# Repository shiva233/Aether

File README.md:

# Aether 🎧
 
A USB-C powered Bluetooth-to-USB audio bridge that lets me connect my phone / Steam Deck with Bluetooth and send that audio straight into my PC as a USB audio input!

|  |  |
| :---: | :---: |
|  |  |

What is Aether? :0

Aether is basically a small USB-C dongle/box thing that pairs to my iPhone, Steam Deck, or other Bluetooth audio source, receives the audio wirelessly, and then sends it to my PC over USB so the computer sees it like a normal USB microphone / audio input device.

I wanted this because very often I want to mix audio from my Steam Deck or phone into my PC headphones while on call with friends or watching a movie, without needing random software, aux cables, capture cards, or weird Windows audio routing. So the idea is that Aether just sits between the device and my PC:

Phone / Steam Deck → Bluetooth → Aether → USB-C → PC → My ears :D

The project is also kind of a challenge project for me because it combines Bluetooth Classic audio, I2S digital audio, USB Audio Class, USB-C power/data, and a custom PCB power tree all in one board :D

## Block Diagram
Coming soon, I promise!! I just need to make a cleaner one!!

## Schematics:

## Layout:

|  |  |
| :---: | :---: |
| <br><b>Top Layer</b> | <br><b>Bottom Layer</b> |
| <br><b>Inner Layer</b> | <br><b>Inner Layer</b> |

Extra Info:

- The Bluetooth Module: Microchip BM83 Bluetooth Stereo Audio Module
- The MCU: STM32C552CET6
- Bluetooth: Bluetooth Classic A2DP Sink
- Audio Path: BM83 decodes Bluetooth audio and outputs digital PCM over I2S
- USB: USB 2.0 Full-Speed device over USB-C
- PC Interface: USB Audio Class input device so Windows can recognize it without custom drivers
- Power: Powered fully from the PC through USB-C VBUS
- BM83 Power Rail: 3.6V Buck Regulator 
- STM32 Power Rail: 3.3V LDO
- Stackup: 4-Layer Custom PCB (Signal - GND - GND - Signal)

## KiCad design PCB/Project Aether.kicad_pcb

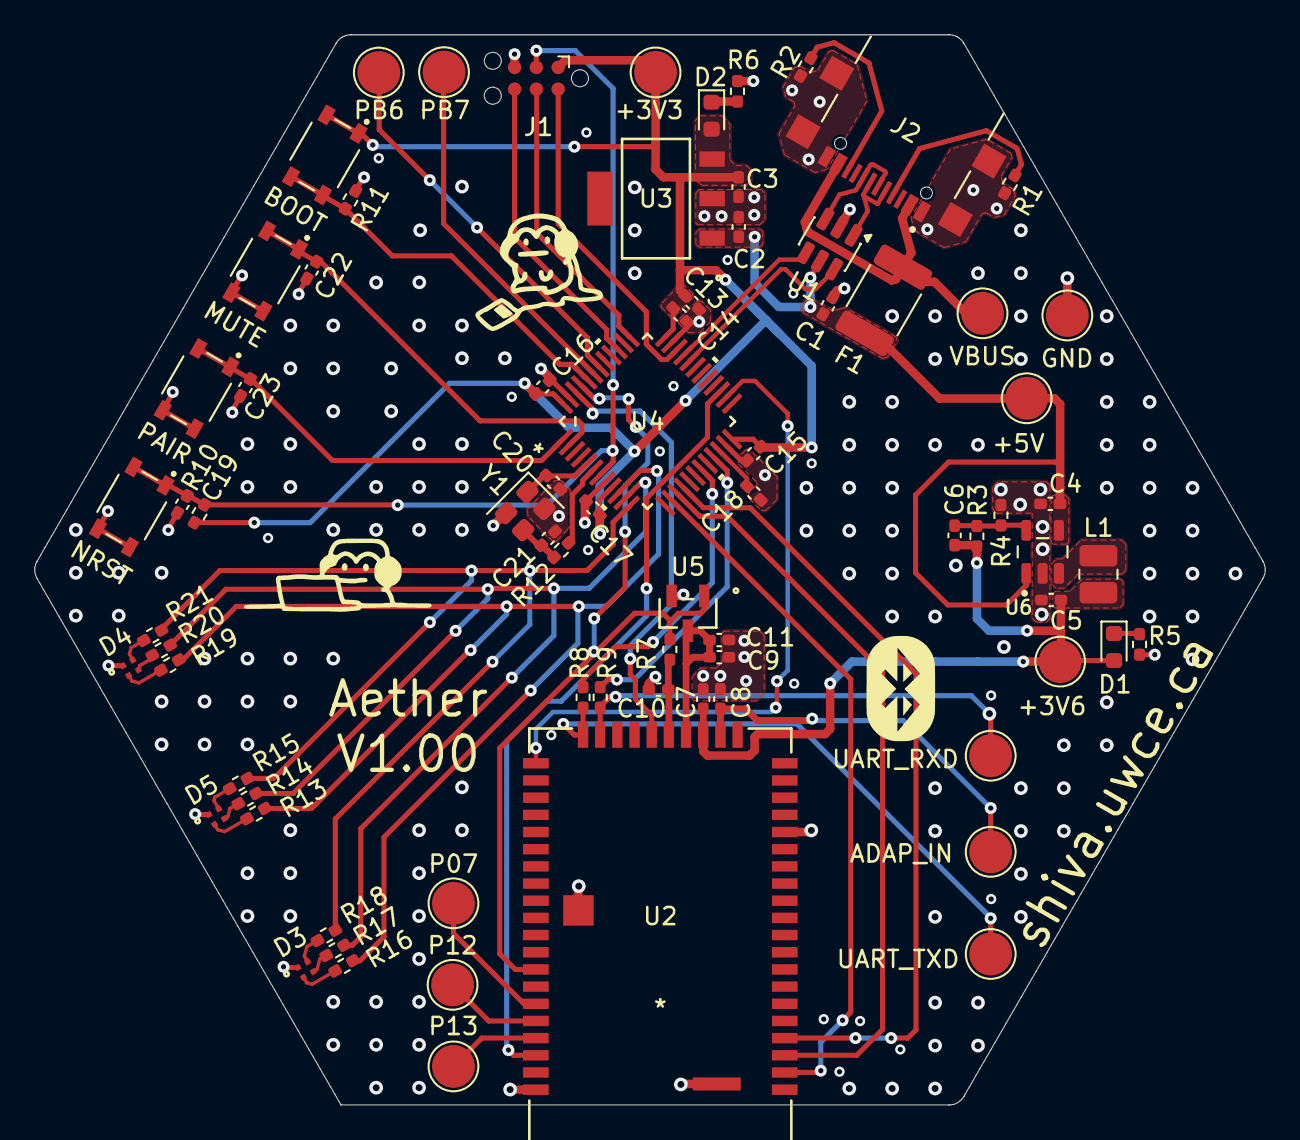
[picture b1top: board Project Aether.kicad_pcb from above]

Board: 4 copper layers, 71.7 x 62.4 mm, 76 parts (0 on the bottom side), 57 nets.

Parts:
+3V3: +3V3; TestPoint_Pad_D2.5mm
+3V6: +3V6; TestPoint_Pad_D2.5mm
+5V: +5V; TestPoint_Pad_D2.5mm
ADAP_IN: TestPoint; TestPoint_Pad_D2.5mm
BOOT: BOOT; SW_SKRPACE010
C1: 100nF; C_0402_1005Metric_Pad0.74x0.62mm_HandSolder
C2, C3, C4, C5: 10uF; C_0402_1005Metric_Pad0.74x0.62mm_HandSolder
C6: DNP; C_0402_1005Metric_Pad0.74x0.62mm_HandSolder
C7, C8: 1uF; C_0402_1005Metric_Pad0.74x0.62mm_HandSolder
C9, C10, C11, C14, C15, C16, C17, C19, C22, C23: 0.1uF; C_0402_1005Metric_Pad0.74x0.62mm_HandSolder
C13: 4.7uF; C_0402_1005Metric_Pad0.74x0.62mm_HandSolder
C18: 2.2uF; C_0402_1005Metric_Pad0.74x0.62mm_HandSolder
C20, C21: 10pF; C_0402_1005Metric_Pad0.74x0.62mm_HandSolder
D1, D2: GREEN; LED_0603_1608Metric
D3, D4, D5: LED_ARGB; SMD4_UHD111A-FKA_CRW
F1: 0.5A HOLD PTC; Fuse_1812_4532Metric_Pad1.30x3.40mm_HandSolder
GND: GND; TestPoint_Pad_D2.5mm
J1: TagConnect; Tag-Connect_TC2030-IDC-NL_2x03_P1.27mm_Vertical
J2: GSB1C41110SSHR; AMPHENOL_GSB1C41110SSHR
L1: 10uH; L_1008_2520Metric
MUTE: MUTE; SW_SKRPACE010
NRST: RESET; SW_SKRPACE010
P07, P12, P13: TestPoint; TestPoint_Pad_D2.5mm
PAIR: PAIR; SW_SKRPACE010
PB6, PB7: TestPoint; TestPoint_Pad_D2.5mm
R1, R2: 5K1; R_0402_1005Metric_Pad0.72x0.64mm_HandSolder
R3: 100k; R_0402_1005Metric_Pad0.72x0.64mm_HandSolder
R4: 20k; R_0402_1005Metric_Pad0.72x0.64mm_HandSolder
R5, R6: 820R; R_0402_1005Metric_Pad0.72x0.64mm_HandSolder
R7: 4.7k; R_0402_1005Metric_Pad0.72x0.64mm_HandSolder
R8, R9, R12: 0R; R_0402_1005Metric_Pad0.72x0.64mm_HandSolder
R10, R11: 10k; R_0402_1005Metric_Pad0.72x0.64mm_HandSolder
R13, R14, R15, R16, R17, R18, R19, R20, R21: TODO; R_0402_1005Metric_Pad0.72x0.64mm_HandSolder
U1: USBLC6-2SC6; SOT-23-6
U2: BM83SM1-00TB; BM83_MCH
U3: MCP1825S-3302E/DB; SOT-223_3MC_MCH
U4: STM32C552CET6; LQFP-48_STM
U5: MCP111T-300E/TT; SOT-23_MC_MCH
U6: TLV62569DBVR; SOT95P280X145-5N
UART_RXD: TestPoint; TestPoint_Pad_D2.5mm
UART_TXD: TestPoint; TestPoint_Pad_D2.5mm
VBUS: VBUS; TestPoint_Pad_D2.5mm
Y1: 16Mhz; Crystal_SMD_2520-4Pin_2.5x2.0mm

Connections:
+3V3: +3V3.1 (1_1), BOOT.1, BOOT.3, C3.2, C13.1, C14.1, C15.1, C16.1, C17.1, D2.2 (A), J1.1 (VCC), R10.1, U3.3 (VOUT), U4.9 (VREF+), U4.24 (VDD), U4.36 (VDD), U4.48 (VDD)
+3V6: +3V6.1 (1_1), C5.2, C6.2, C7.1, D1.2 (A), L1.2, R3.1, U2.23 (BAT_IN)
+5V: +5V.1 (1_1), C1.2, C2.2, C4.2, F1.2, U1.5 (VBUS), U3.1 (VIN), U6.1 (EN), U6.4 (VIN)
/MCU/BM83_ADAP_IN: ADAP_IN.1 (1_1), C8.1, U2.22 (ADAP_IN)
/MCU/BM83_MFB: U2.26 (PWR(MFB)), U4.46 (PB9)
/MCU/BM83_P0_7: P07.1 (1_1), U2.45 (P0_7)
/MCU/BM83_P1_2: P12.1 (1_1), U2.46 (P1_2/TDI_CPU/SCL)
/MCU/BM83_P1_3: P13.1 (1_1), U2.47 (P1_3/TCK_CPU/SDA)
/MCU/BM83_RESET_N: R7.2, U2.43 (RST_N), U4.45 (PB8), U5.1 (VOUT)
/MCU/BM83_UART_RXD: R9.2, U2.29 (P8_6/UART_RXD), UART_RXD.1 (1_1)
/MCU/BM83_UART_TXD: R8.2, U2.30 (P8_5/UART_TXD), UART_TXD.1 (1_1)
/MCU/STM_BOOT0: BOOT.2, BOOT.4, R11.1, U4.44 (PH2-BOOT0)
/MCU/STM_HSE_IN: C20.1, U4.5 (PH0-OSC_IN), Y1.1
/MCU/STM_HSE_OUT: R12.1, U4.6 (PH1-OSC_OUT)
/MCU/STM_I2S_CK: U2.3 (SCLK1), U4.15 (PA5)
/MCU/STM_I2S_SDI: U2.4 (DT1), U4.16 (PA6)
/MCU/STM_I2S_WS: U2.2 (RFS1), U4.14 (PA4)
/MCU/STM_MUTE_BTN: C22.1, MUTE.1, MUTE.3, U4.2 (PC13)
/MCU/STM_NRST: C19.1, J1.3 (~RESET), NRST.1, NRST.3, R10.2, U4.7 (NRST)
/MCU/STM_PAIR_BTN: C23.1, PAIR.1, PAIR.3, U4.1 (PE2)
/MCU/STM_PB6: PB6.1 (1_1), U4.42 (PB6)
/MCU/STM_PB7: PB7.1 (1_1), U4.43 (PB7)
/MCU/STM_RGB_B: R15.1, R18.1, R21.1, U4.12 (PA2)
/MCU/STM_RGB_G: R14.1, R17.1, R20.1, U4.11 (PA1)
/MCU/STM_RGB_R: R13.1, R16.1, R19.1, U4.10 (PA0)
/MCU/STM_SWCLK: J1.4 (SWCLK), U4.37 (PA14)
/MCU/STM_SWDIO: J1.2 (SWDIO), U4.34 (PA13)
/MCU/STM_SWO: J1.6 (SWO), U4.39 (PB3)
/MCU/STM_UART_CTS: U2.31 (P3_4/UART_RTS), U4.26 (PB13)
/MCU/STM_UART_RTS: U2.48 (P3_7/UART_CTS), U4.27 (PB14)
/MCU/STM_UART_RXD: R8.1, U4.19 (PB1)
/MCU/STM_UART_TXD: R9.1, U4.21 (PB10)
/MCU/XTAL_IN: C21.1, R12.2, Y1.3
/USB-C + Power/BUCK_FB: C6.1, R3.2, R4.1, U6.5 (FB)
/USB-C + Power/BUCK_SW: L1.1, U6.3 (SW)
/USB-C + Power/LED_3V3_K: D2.1 (K), R6.1
/USB-C + Power/LED_3V6_K: D1.1 (K), R5.1
/USB-C + Power/USB_CC1: J2.A5 (CC1), R1.1
/USB-C + Power/USB_CC2: J2.B5 (CC2), R2.1
/USB-C + Power/USB_D_N: J2.A7 (DN1), J2.B7 (DN2), U1.1 (I/O1)
/USB-C + Power/USB_D_P: J2.A6 (DP1), J2.B6 (DP2), U1.3 (I/O2)
GND: C1.1, C2.1, C3.1, C4.1, C5.1, C7.2, C8.2, C9.2, C10.2, C11.2, C13.2, C14.2, C15.2, C16.2, C17.2, C18.2, C19.2, C20.2, C21.2, C22.2, C23.2, D3.1 (A), D4.1 (A), D5.1 (A), GND.1 (1_1), J1.5 (GND), J2.A1_B12 (GND_A), J2.B1_A12 (GND_B), J2.SH1 (SHIELD), J2.SH2 (SHIELD__1), J2.SH3 (SHIELD__2), J2.SH4 (SHIELD__3), MUTE.2, MUTE.4, NRST.2, NRST.4, PAIR.2, PAIR.4, R1.2, R2.2, R4.2, R5.2, R6.2, R11.2, U1.2 (GND), U2.16 (GND), U2.50 (GND), U2.56 (GND), U2.57 (GND), U3.2 (GND), U4.8 (VREF-), U4.23 (VSS), U4.35 (VSS), U4.47 (VSS), U5.2 (VSS), U6.2 (GND), Y1.2 (G), Y1.4 (G)
unnamed: D3.4 (BK), R18.2
unnamed: D3.3 (GK), R17.2
unnamed: D3.2 (RK), R16.2
unnamed: D4.4 (BK), R21.2
unnamed: D4.3 (GK), R20.2
unnamed: D4.2 (RK), R19.2
unnamed: D5.4 (BK), R15.2
unnamed: D5.3 (GK), R14.2
unnamed: D5.2 (RK), R13.2
unnamed: C18.1, U4.22 (VCAP)
STM_D_N: U1.6 (I/O1), U4.32 (PA11)
STM_D_P: U1.4 (I/O2), U4.33 (PA12)
SYS_PWR: C9.1, C11.1, U2.24 (SYS_PWR), U5.3 (VDD)
VBUS: F1.1, J2.A4_B9 (VBUS_A), J2.B4_A9 (VBUS_B), VBUS.1 (1_1)
VDD_IO: C10.1, R7.1, U2.25 (VDD_IO)

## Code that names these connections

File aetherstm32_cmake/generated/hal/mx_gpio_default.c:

/**
  ******************************************************************************
  * @file           : mx_gpio_default.c
  * @brief          : gpio_default Peripheral initialization
  ******************************************************************************
  * @attention
  *
  * Copyright (c) 2026 STMicroelectronics.
  * All rights reserved.
  *
  * This software is licensed under terms that can be found in the mx_stm32c5xx_hal_drivers_license.md file
  * in the same directory as the generated code.
  * If no mx_stm32c5xx_hal_drivers_license.md file comes with this software, it is provided AS-IS.
  *
  ******************************************************************************
  */

/* Includes ------------------------------------------------------------------*/
#include "mx_gpio_default.h"

/* Exported types ------------------------------------------------------------*/
/* Exported constants --------------------------------------------------------*/
/* Private define ------------------------------------------------------------*/
/* Private functions ---------------------------------------------------------*/
/* Exported variables by reference -------------------------------------------*/

/******************************************************************************/
/* Exported functions for GPIO in HAL layer (SW instance MyGPIO_1) */
/******************************************************************************/
system_status_t mx_gpio_default_init(void)
{
  hal_gpio_config_t  gpio_config;

  HAL_RCC_GPIOA_EnableClock();

  HAL_RCC_GPIOC_EnableClock();

  HAL_RCC_GPIOE_EnableClock();

  /* Configure PA0, PA1, PA2 GPIO pins in input mode */
  gpio_config.mode            = HAL_GPIO_MODE_INPUT;
  gpio_config.pull            = HAL_GPIO_PULL_NO;
  if (HAL_GPIO_Init(HAL_GPIOA, HAL_GPIO_PIN_0 | HAL_GPIO_PIN_1 | HAL_GPIO_PIN_2, &gpio_config) != HAL_OK)
  {
    return SYSTEM_PERIPHERAL_ERROR;
  }

  /*
    GPIO pin labels :
    PC13  ---------> MUTE_BTN
    PC14  ---------> BM83_MFB
    PC15  ---------> BM83_RESET
    */
  /* Configure PC13, PC14, PC15 GPIO pins in input mode */
  gpio_config.mode            = HAL_GPIO_MODE_INPUT;
  gpio_config.pull            = HAL_GPIO_PULL_NO;
  if (HAL_GPIO_Init(HAL_GPIOC, HAL_GPIO_PIN_13 | HAL_GPIO_PIN_14 | HAL_GPIO_PIN_15, &gpio_config) != HAL_OK)
  {
    return SYSTEM_PERIPHERAL_ERROR;
  }

  /*
    GPIO pin labels :
    PE2   ---------> PAIR_BTN
    */
  /* Configure PE2 GPIO pin in input mode */
  gpio_config.mode            = HAL_GPIO_MODE_INPUT;
  gpio_config.pull            = HAL_GPIO_PULL_NO;
  if (HAL_GPIO_Init(PAIR_BTN_PORT, PAIR_BTN_PIN, &gpio_config) != HAL_OK)
  {
    return SYSTEM_PERIPHERAL_ERROR;
  }

  return SYSTEM_OK;
}

system_status_t mx_gpio_default_deinit(void)
{
  /* De-initialize pins of GPIOA port */
  HAL_GPIO_DeInit(HAL_GPIOA, HAL_GPIO_PIN_0 | HAL_GPIO_PIN_1 | HAL_GPIO_PIN_2);

  /* De-initialize pins of GPIOC port */
  HAL_GPIO_DeInit(HAL_GPIOC, HAL_GPIO_PIN_13 | HAL_GPIO_PIN_14 | HAL_GPIO_PIN_15);

  /* De-initialize pins of GPIOE port */
  HAL_GPIO_DeInit(HAL_GPIOE, HAL_GPIO_PIN_2);

  return SYSTEM_OK;
}

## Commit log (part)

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2026-06-06 Reorganizing Files
2026-06-06 STM32CUBEMX Pinout
2026-06-06 Fixed Buck Converter + Assigned stm32 pinout
2026-06-07 Updated stm32mx
2026-06-07 More schematic work
2026-06-08 fixed usb global label + some readability stuff on schematic
2026-06-08 fixed some footprints
2026-06-08 Assigned all footprints, deleted user interface schematic
2026-06-08 started layout and made adjustments to a few footprints + small schematic changes
2026-06-08 More progress on layout + added resistors to rgb cuz I forgot
2026-06-09 iterated on part of the layout
2026-06-10 good amount of progress on layout
2026-06-10 commit before hexagoning
2026-06-10 hexagon now! :D
2026-06-10 last commit tonight!
2026-06-11 finished pre fedevel routing
2026-06-12 Added design rules and constraints and default values from fedevel video
2026-06-12 fixed some bs that I forgot to route
2026-06-12 Finished placing and routing all the test points at the top and some other pins I forgot to route
2026-06-12 wroked on buck layour
2026-06-12 Finished placement/layout of buck roughl version
2026-06-12 i hate everything
2026-06-13 sfjhksdf
2026-06-13 power puddles and redoing ground vias
2026-06-14 more progress on layout
2026-06-29 changed board stack up
